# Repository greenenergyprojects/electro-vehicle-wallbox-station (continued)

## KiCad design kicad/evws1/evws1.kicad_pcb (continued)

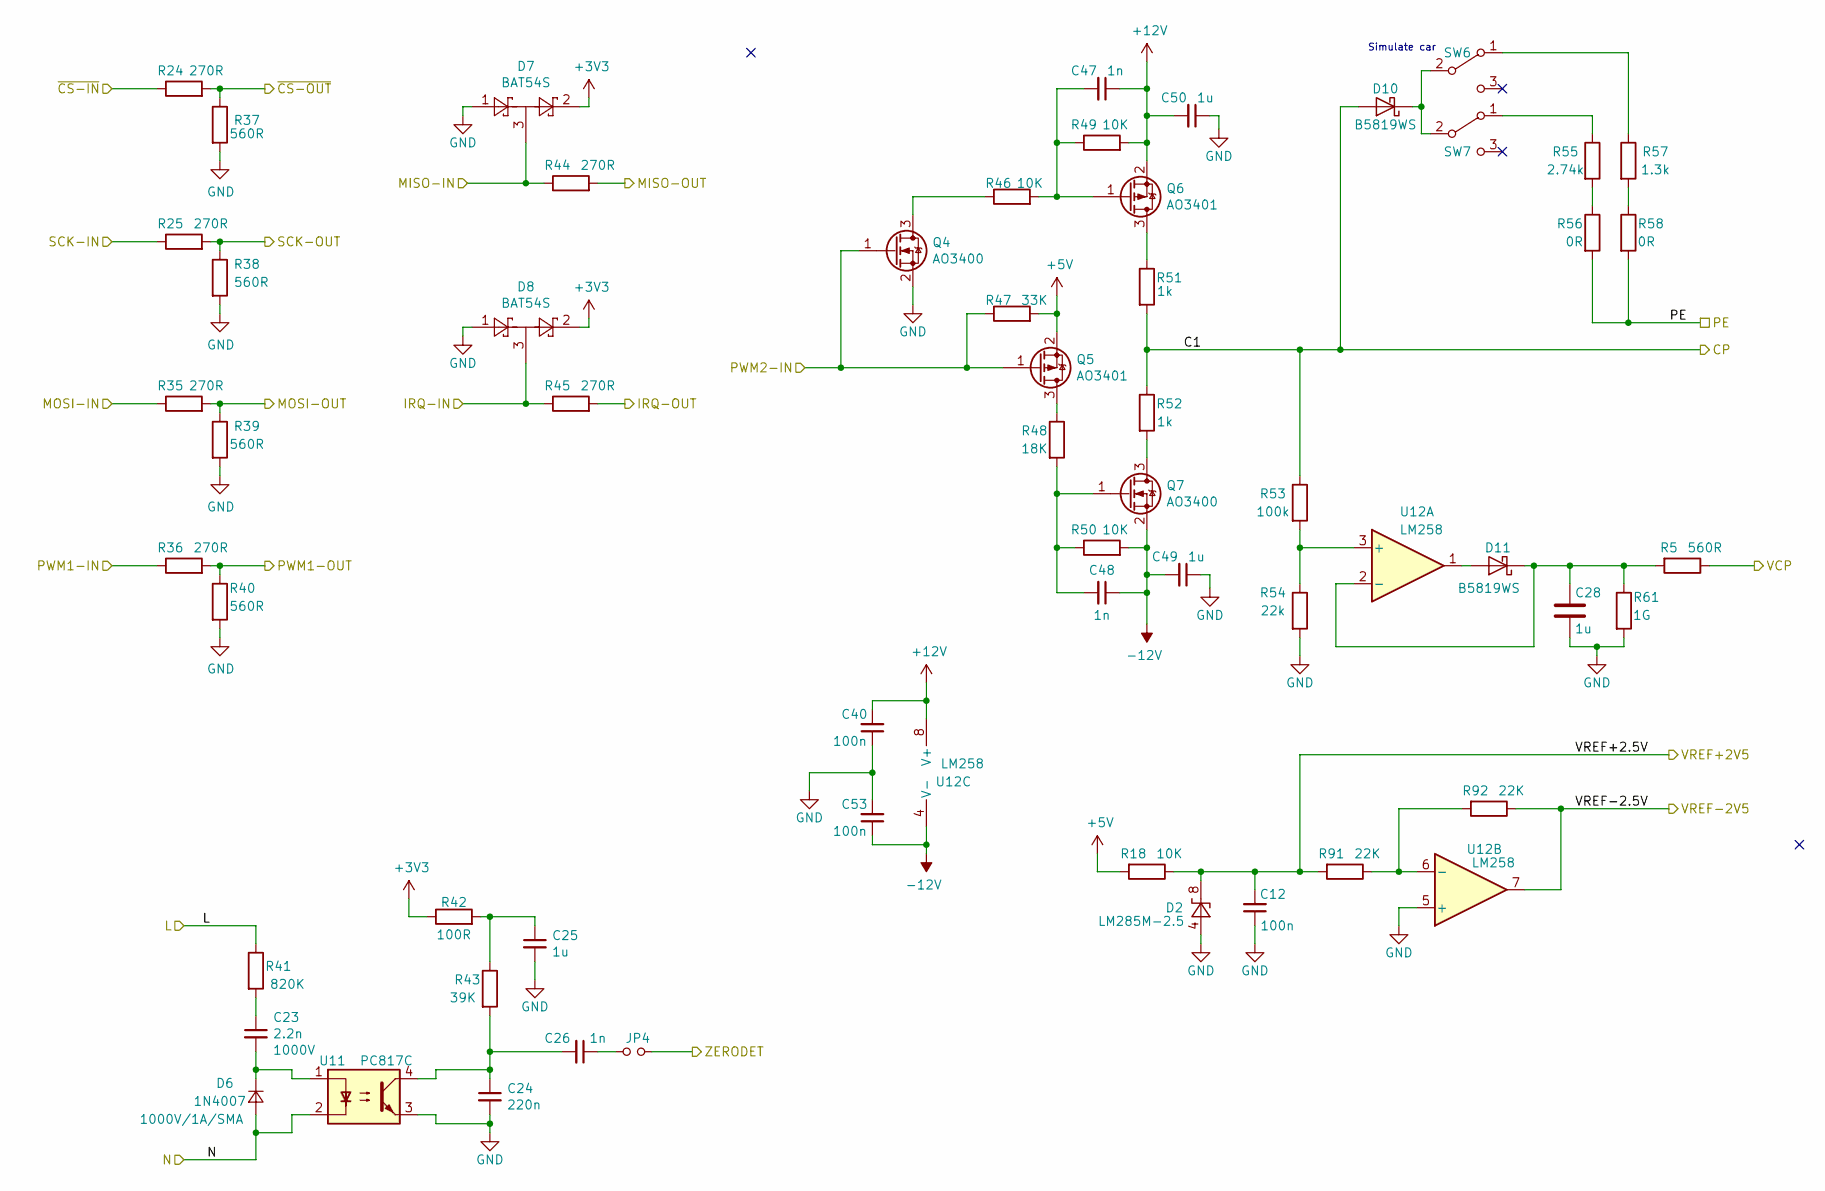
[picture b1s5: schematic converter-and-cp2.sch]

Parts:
C12, C40, C53: 100n; c-1206-hand-soldering
C23: 2.2n; c-1206-hand-soldering
C24: 220n; c-1206-hand-soldering
C25, C28, C49, C50: 1u; c-1206-hand-soldering
C26, C47, C48: 1n; c-1206-hand-soldering
D2: LM285M-2.5; SOIC-8_3.9x4.9mm_Pitch1.27mm_Handsolded
D6: 1N4007; sma_hand-soldering
D7, D8: BAT54S; sot-23_hand-soldering
D10, D11: B5819WS; sod-323_hand-soldering
JP4: Jumper_NO_Small; idc-header-1x02-p2.54mm-vertical
Q4, Q7: AO3400; sot-23_hand-soldering
Q5, Q6: AO3401; sot-23_hand-soldering
R5, R37, R38, R39, R40: 560R; r-1206-hand-soldering
R18, R46, R49, R50: 10K; r-1206-hand-soldering
R24, R25, R35, R36, R44, R45: 270R; r-1206-hand-soldering
R41: 820K; r-1206-hand-soldering
R42: 100R; r-1206-hand-soldering
R43: 39K; r-1206-hand-soldering
R47: 33K; r-1206-hand-soldering
R48: 18K; r-1206-hand-soldering
R51, R52: 1k; r-1206-hand-soldering
R53: 100k; r-1206-hand-soldering
R54: 22k; r-1206-hand-soldering
R55: 2.74k; r-1206-hand-soldering
R56, R58: 0R; r-1206-hand-soldering
R57: 1.3k; r-1206-hand-soldering
R61: 1G; r-1206-hand-soldering
R91, R92: 22K; r-1206-hand-soldering
SW6, SW7: SS-12D00G3; switch_ss-12d00g3
U11: PC817C; sop-4-pc817
U12: LM258; soic-8_hand-soldering

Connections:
230V-L: R41.1; also elsewhere on the board
230V-N: D6.2 (A), U11.2; also elsewhere on the board
+5V: Q5.2 (S), R18.2, R47.2; also elsewhere on the board
+12V: C40.2, C47.1, C50.2, Q6.2 (S), R49.2, U12.8 (V+); also elsewhere on the board
-12V: C48.1, C49.2, C53.1, Q7.2 (S), R50.2, U12.4 (V-); also elsewhere on the board
/CP1: D10.2 (A), R51.2, R52.1, R53.1; also elsewhere on the board
/Measurement/VREF+2V5: C12.2, D2.8 (K), R18.1, R91.2; also elsewhere on the board
/Measurement/VREF-2V5: R92.1, U12.7; also elsewhere on the board
/Microcontroller/AD-VC1: R5.1; also elsewhere on the board
/Microcontroller/Converter-And-Cp/IRQ-IN: D8.3, R45.1; also elsewhere on the board
/Microcontroller/Converter-And-Cp/MISO-IN: D7.3, R44.1; also elsewhere on the board
/Microcontroller/Converter-And-Cp/MOSI-OUT: R35.2, R39.1; also elsewhere on the board
/Microcontroller/Converter-And-Cp/PWM1-OUT: R36.2, R40.1; also elsewhere on the board
/Microcontroller/Converter-And-Cp/SCK-OUT: R25.2, R38.1; also elsewhere on the board
/Microcontroller/Converter-And-Cp/~CS-OUT: R24.2, R37.1; also elsewhere on the board
/Microcontroller/IRQ-MODEM: R45.2; also elsewhere on the board
/Microcontroller/MISO: R44.2; also elsewhere on the board
/Microcontroller/MOSI: R35.1; also elsewhere on the board
/Microcontroller/PWM1: R36.1; also elsewhere on the board
/Microcontroller/PWM2: Q4.1 (G), Q5.1 (G), R47.1; also elsewhere on the board
/Microcontroller/SCK: R25.1; also elsewhere on the board
/Microcontroller/ZERODET: JP4.2; also elsewhere on the board
/Microcontroller/~SCS: R24.1; also elsewhere on the board
GND: C12.1, C24.2, C25.2, C28.2, C40.1, C49.1, C50.1, C53.2, D2.4 (A), D7.1, D8.1, Q4.2 (S), R37.2, R38.2, R39.2, R40.2, R54.2, R61.2, U11.3, U12.5 (+); also elsewhere on the board
unnamed: C23.1, R41.2
unnamed: C23.2, D6.1 (K), U11.1
unnamed: C24.1, C26.2, R43.2, U11.4
unnamed: C25.1, R42.2, R43.1
unnamed: C26.1, JP4.1
unnamed: C28.1, D11.1 (K), R5.2, R61.1, U12.2 (-)
unnamed: C47.2, Q6.1 (G), R46.2, R49.1
unnamed: C48.2, Q7.1 (G), R48.2, R50.1
unnamed: D10.1 (K), SW6.2 (B), SW7.2 (B)
unnamed: D11.2 (A), U12.1
unnamed: Q4.3 (D), R46.1
unnamed: Q5.3 (D), R48.1
unnamed: Q6.3 (D), R51.1
unnamed: Q7.3 (D), R52.2
unnamed: R53.2, R54.1, U12.3 (+)
unnamed: R55.1, SW7.1 (A)
unnamed: R55.2, R56.1
unnamed: R57.1, SW6.1 (A)
unnamed: R57.2, R58.1
unnamed: R91.1, R92.2, U12.6 (-)
PE: R56.2, R58.2; also elsewhere on the board

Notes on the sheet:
Simulate car

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
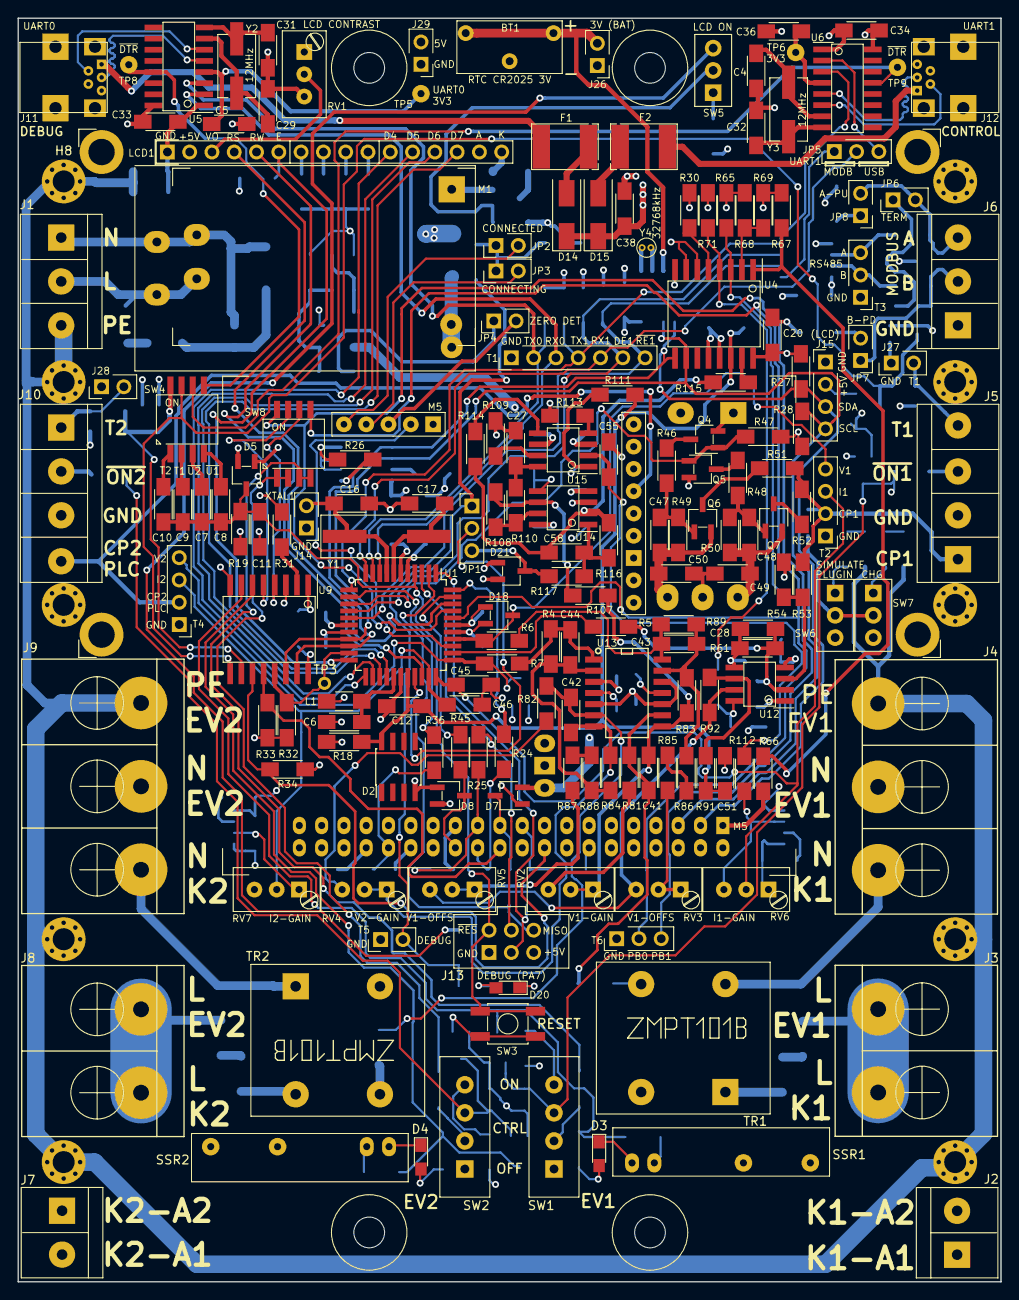
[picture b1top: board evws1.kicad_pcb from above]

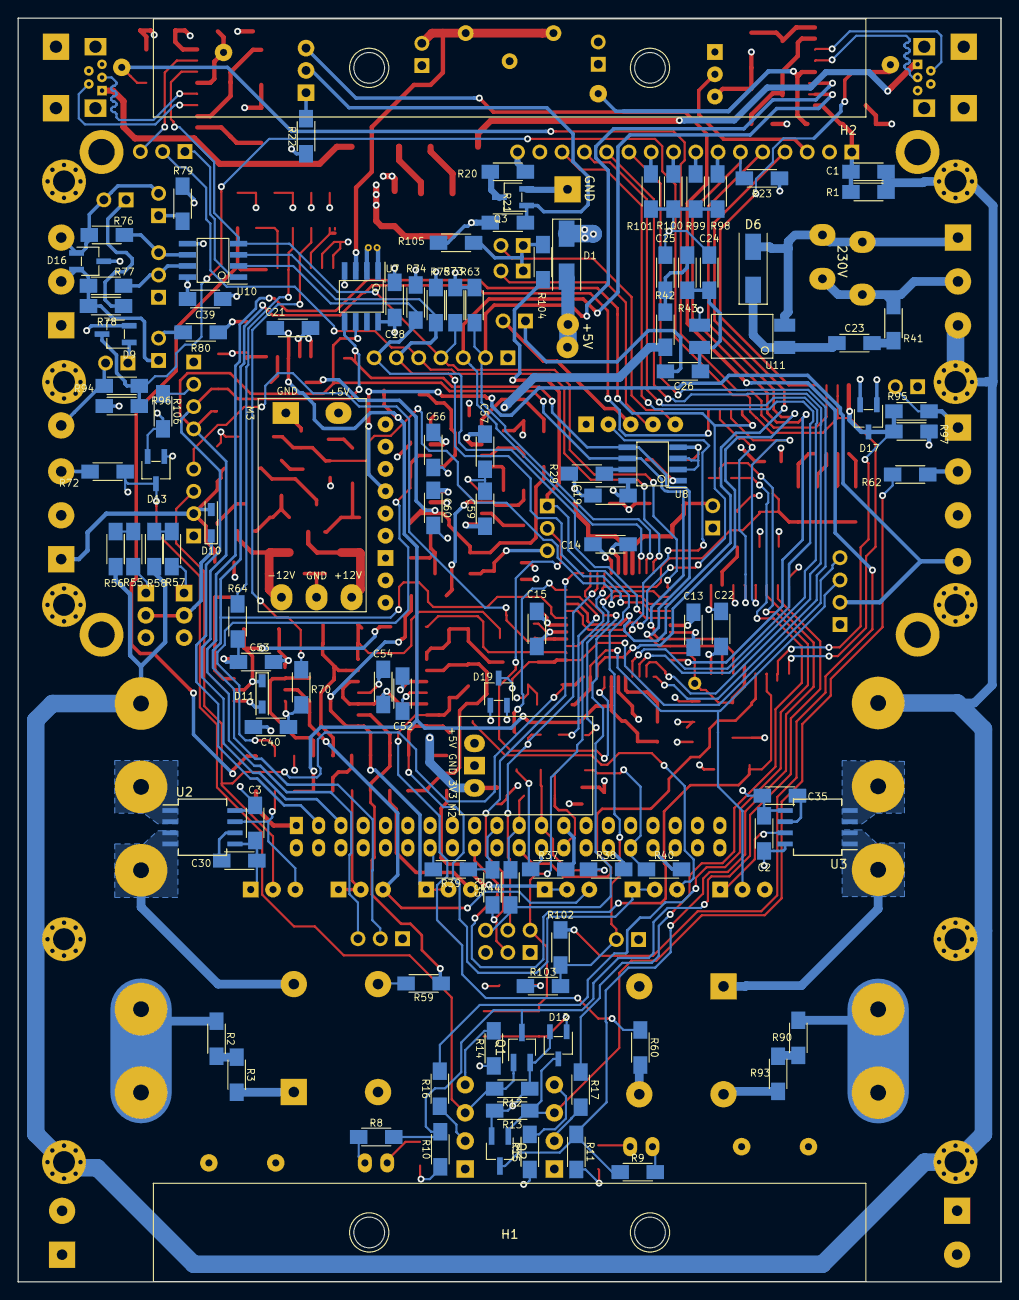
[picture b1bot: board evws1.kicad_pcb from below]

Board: 4 copper layers, 112.0 x 144.0 mm, 301 parts (109 on the bottom side), 202 nets.

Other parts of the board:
T6: header; idc-header-1x03-p2.54mm-vertical

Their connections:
GND: T6.1; also elsewhere on the board
unnamed 147: T6.2; also elsewhere on the board
unnamed 148: T6.3; also elsewhere on the board

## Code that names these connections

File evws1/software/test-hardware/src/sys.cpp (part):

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    
    void init () {
        memset((void *)&sys, 0, sizeof(sys));
	DDRB |= (1 << PB1); // test signal

	DDRB |= (1 << PB0); // ~K1-ON via SW6D or Life-LED via JP9
	
        UBRR0L = (F_CPU / GLOBAL_UART0_BITRATE + 4) / 8 - 1;
        UBRR0H = 0x00;
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
    // LCD-Display 4x20 Zeichen, 5x8 Pixel/Zeichen
    // Controller KS0076B
    // Data: Port C (PC7:4 = D7:4)
    // RS=PB2, RW=PA6, E=PC3, VO (Kontrast) ueber Poti, Backlight PB1 (via T6)

    const uint8_t LCD_PULSE_LENGTH = 15;
    #define LCD_DATA_IN  DDRC &= ~0xf0;    
    #define LCD_DATA_OUT DDRC |= 0xf0;
    #define LCD_SET_DATA(x) PORTC = (PORTC & 0x0f) | ((x) << 4);
    #define LCD_RS_OUT   DDRB  |=  (1 << PB2);
    #define LCD_SET_RS   PORTB |=  (1 << PB2); // Signal RS=1
    #define LCD_CLR_RS   PORTB &= ~(1 << PB2); // Signal RS=0
    #define LCD_RW_OUT   DDRA  |=  (1 << PA6);
    #define LCD_SET_RW   PORTA |=  (1 << PA6); // Signal RW=1
    #define LCD_CLR_RW   PORTA &= ~(1 << PA6); // Signal RW=0
    #define LCD_E_OUT    DDRC  |=  (1 << PC3);    
    #define LCD_SET_E    PORTC |=  (1 << PC3); // Signal E=1 
    #define LCD_CLR_E    PORTC &= ~(1 << PC3); // Signal E=0 

    const uint8_t LCD_CMD_DISPLAY_CLEAR  = 0x01;  // Display clear
    const uint8_t LCD_CMD_CURSOR_HOME    = 0x02;  // Move cursor digit 1
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    // ----------------------------------------------------------------------
    
    void toggleLifeLed () {
	PORTB ^= (1 << PB0);
    }
    
    void setLifeLed (bool on) {
	if (on) {
	    PORTB |= (1 << PB0);
	} else {
	    PORTB &= ~(1 << PB0);
	}
    }
    
    void togglePB1 () {
	PORTB ^= (1 << PB1);
    }
    
    void setPB1 (bool on) {
	if (on) {
	    PORTB |= (1 << PB1);
	} else {
	    PORTB &= ~(1 << PB1);
	}
    }

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
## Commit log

2019-12-09 project initialization
2020-01-31 Schematic completed, no DRC errors left
2020-02-03 schematic finished
2020-02-17 schematic finished, placement finished
2020-02-21 first routing finished, clean DRC
2020-02-23 V1.0 Design finished
2020-02-23 Renaming kicad/evws1 -> evws1/kicad
2020-02-23 fixing project problems, cause by renaming directory
2020-02-23 Tapeout V1.0
2021-01-19 kicad/dist/README.md updated
2021-01-19 software/test-hardware added
2021-01-19 Software evws1/software/atmega324p_u1 added (from fiv-template)
2022-04-08 sx-2021-01-19
2022-04-09 update docs...
